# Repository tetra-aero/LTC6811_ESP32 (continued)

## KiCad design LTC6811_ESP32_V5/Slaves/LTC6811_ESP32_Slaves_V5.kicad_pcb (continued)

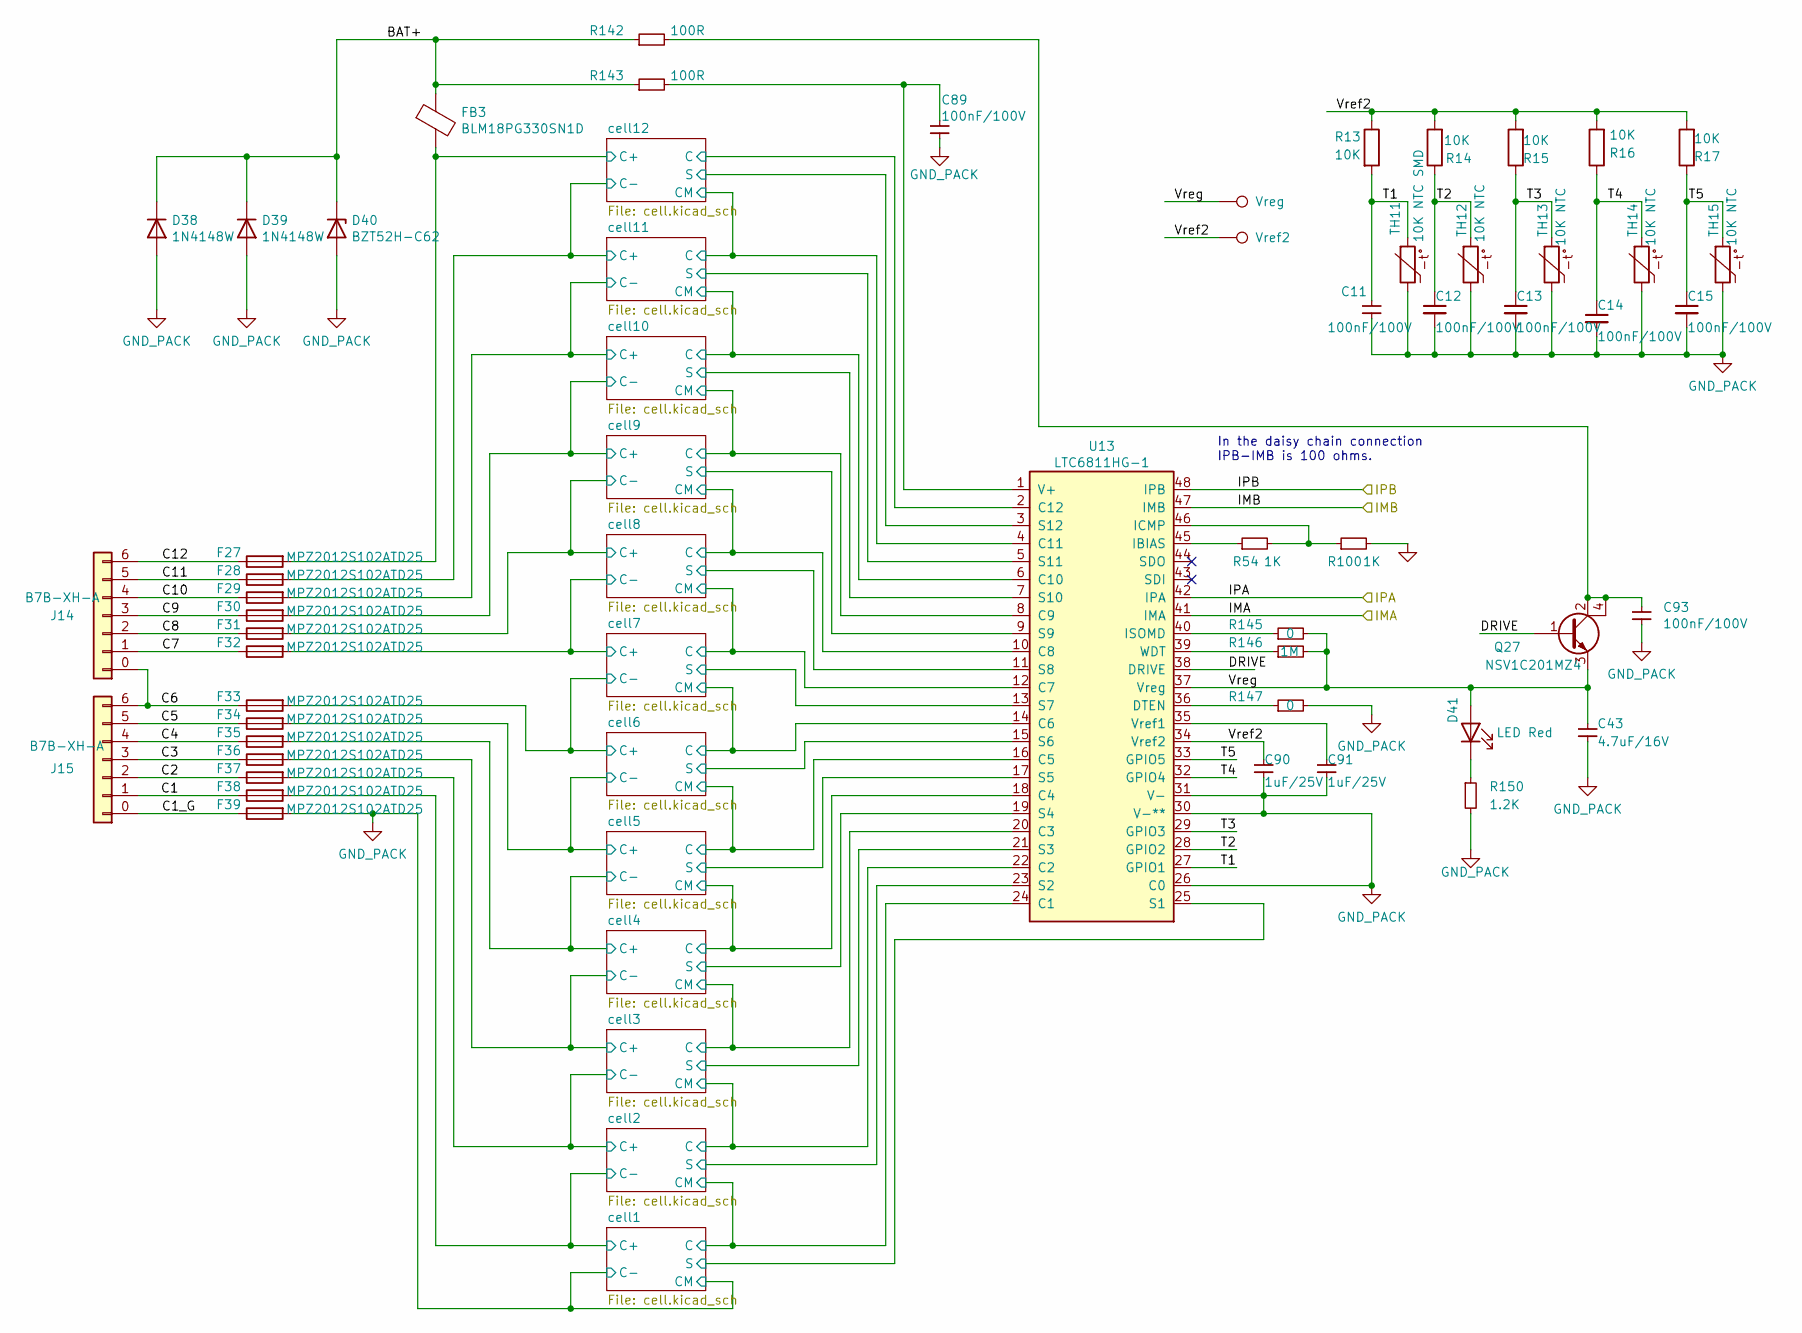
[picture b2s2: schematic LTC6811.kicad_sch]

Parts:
C11, C12, C13, C14, C15, C89, C93: 100nF/100V; C_0603_1608Metric; MPN CL10B104KC8NNNC
C43: 4.7uF/16V; C_0603_1608Metric; MPN CL10A475KO8NNNC
C90, C91: 1uF/25V; C_0603_1608Metric; MPN CL10B105KA8NNNC
D38, D39: 1N4148W; D_SOD-123; MPN 1N4148W-7-F
D40: BZT52H-C62; D_SOD-123F; MPN BZT52H-C62,115
D41: LED Red; LED_0603_1608Metric; MPN LTST-C190KRKT
F27, F28, F29, F30, F31, F32, F33, F34, F35, F36, F37, F38, F39: MPZ2012S102ATD25; Fuse_0805_2012Metric; MPN MPZ2012S102ATD25
FB3: BLM18PG330SN1D; R_0603_1608Metric; MPN BLM18PG330SN1D
J14, J15: B7B-XH-A; JST_XH_B7B-XH-A_1x07_P2.50mm_Vertical_BAT_6S; MPN B7B-XH-A
Q27: NSV1C201MZ4; SOT-223; MPN NSV1C201MZ4T1G
R13, R14, R15, R16, R17: 10K; R_0603_1608Metric; MPN RC0603FR-0710KL
R54, R100: 1K; R_0603_1608Metric; MPN RC0603FR-071KL
R142, R143: 100R; R_0603_1608Metric; MPN RC0603FR-07100RL
R145, R147: 0; R_0603_1608Metric; MPN RC0603JR-070RL
R146: 1M; R_0603_1608Metric; MPN RC0603JR-071ML
R150: 1.2K; R_0603_1608Metric; MPN RC0603JR-071K2L
TH11: 10K NTC SMD; R_0603_1608Metric; MPN NCU18XH103F6SRB
TH12, TH13, TH14, TH15: 10K NTC; R_Axial_DIN0204_L3.6mm_D1.6mm_P1.90mm_Vertical; MPN MF52C1103F3380
TP7: Vreg; TestPoint_Pad_D1.0mm
TP8: Vref2; TestPoint_Pad_D1.0mm
U13: LTC6811HG-1; TSSOP-48_6.1x12.5mm_P0.5mm; MPN LTC6811HG-1#3ZZPBF

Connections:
/LTC6811_3/BAT+: D38.1 (K), D39.1 (K), D40.1 (K), FB3.1, R142.1, R143.1
/LTC6811_3/C1: F38.1, J15.1 (Pin_2)
/LTC6811_3/C1_G: F39.1, J15.0 (Pin_1)
/LTC6811_3/C2: F37.1, J15.2 (Pin_3)
/LTC6811_3/C3: F36.1, J15.3 (Pin_4)
/LTC6811_3/C4: F35.1, J15.4 (Pin_5)
/LTC6811_3/C5: F34.1, J15.5 (Pin_6)
/LTC6811_3/C6: F33.1, J14.0 (Pin_1), J15.6 (Pin_7)
/LTC6811_3/C7: F32.1, J14.1 (Pin_2)
/LTC6811_3/C8: F31.1, J14.2 (Pin_3)
/LTC6811_3/C9: F30.1, J14.3 (Pin_4)
/LTC6811_3/C10: F29.1, J14.4 (Pin_5)
/LTC6811_3/C11: F28.1, J14.5 (Pin_6)
/LTC6811_3/C12: F27.1, J14.6 (Pin_7)
/LTC6811_3/DRIVE: Q27.1 (B), U13.38 (DRIVE)
/LTC6811_3/IMA: U13.41 (IMA); also elsewhere on the board
/LTC6811_3/IMB: U13.47 (IMB); also elsewhere on the board
/LTC6811_3/IPA: U13.42 (IPA); also elsewhere on the board
/LTC6811_3/IPB: U13.48 (IPB); also elsewhere on the board
/LTC6811_3/T1: C11.1, R13.2, TH11.1, U13.27 (GPIO1)
/LTC6811_3/T2: C12.1, R14.1, TH12.1, U13.28 (GPIO2)
/LTC6811_3/T3: C13.1, R15.1, TH13.1, U13.29 (GPIO3)
/LTC6811_3/T4: C14.1, R16.1, TH14.1, U13.32 (GPIO4)
/LTC6811_3/T5: C15.1, R17.1, TH15.1, U13.33 (GPIO5)
/LTC6811_3/Vref2: C90.1, R13.1, R14.2, R15.2, R16.2, R17.2, TP8.1, U13.34 (Vref2)
/LTC6811_3/Vreg: C43.1, D41.2 (A), Q27.3 (E), R145.2, R146.2, TP7.1, U13.37 (Vreg)
/LTC6811_3/cell1/C: U13.24 (C1); also elsewhere on the board
/LTC6811_3/cell1/C+: F38.2; also elsewhere on the board
/LTC6811_3/cell1/S: U13.25 (S1); also elsewhere on the board
/LTC6811_3/cell2/C: U13.22 (C2); also elsewhere on the board
/LTC6811_3/cell2/C+: F37.2; also elsewhere on the board
/LTC6811_3/cell2/S: U13.23 (S2); also elsewhere on the board
/LTC6811_3/cell3/C: U13.20 (C3); also elsewhere on the board
/LTC6811_3/cell3/C+: F36.2; also elsewhere on the board
/LTC6811_3/cell3/S: U13.21 (S3); also elsewhere on the board
/LTC6811_3/cell4/C: U13.18 (C4); also elsewhere on the board
/LTC6811_3/cell4/C+: F35.2; also elsewhere on the board
/LTC6811_3/cell4/S: U13.19 (S4); also elsewhere on the board
/LTC6811_3/cell5/C: U13.16 (C5); also elsewhere on the board
/LTC6811_3/cell5/C+: F34.2; also elsewhere on the board
/LTC6811_3/cell5/S: U13.17 (S5); also elsewhere on the board
/LTC6811_3/cell6/C: U13.14 (C6); also elsewhere on the board
/LTC6811_3/cell6/C+: F33.2; also elsewhere on the board
/LTC6811_3/cell6/S: U13.15 (S6); also elsewhere on the board
/LTC6811_3/cell7/C: U13.12 (C7); also elsewhere on the board
/LTC6811_3/cell7/C+: F32.2; also elsewhere on the board
/LTC6811_3/cell7/S: U13.13 (S7); also elsewhere on the board
/LTC6811_3/cell8/C: U13.10 (C8); also elsewhere on the board
/LTC6811_3/cell8/C+: F31.2; also elsewhere on the board
/LTC6811_3/cell8/S: U13.11 (S8); also elsewhere on the board
/LTC6811_3/cell9/S: U13.9 (S9); also elsewhere on the board
/LTC6811_3/cell10/C: U13.6 (C10); also elsewhere on the board
/LTC6811_3/cell10/C+: F29.2; also elsewhere on the board
/LTC6811_3/cell10/C-: F30.2; also elsewhere on the board
/LTC6811_3/cell10/CM: U13.8 (C9); also elsewhere on the board
/LTC6811_3/cell10/S: U13.7 (S10); also elsewhere on the board
/LTC6811_3/cell11/C: U13.4 (C11); also elsewhere on the board
/LTC6811_3/cell11/C+: F28.2; also elsewhere on the board
/LTC6811_3/cell11/S: U13.5 (S11); also elsewhere on the board
/LTC6811_3/cell12/C: U13.2 (C12); also elsewhere on the board
/LTC6811_3/cell12/C+: F27.2, FB3.2; also elsewhere on the board
/LTC6811_3/cell12/S: U13.3 (S12); also elsewhere on the board
GND_PACK: C11.2, C12.2, C13.2, C14.2, C15.2, C43.2, C89.2, C90.2, C91.2, C93.2, D38.2 (A), D39.2 (A), D40.2 (A), F39.2, R100.2, R147.2, R150.2, TH11.2, TH12.2, TH13.2, TH14.2, TH15.2, U13.26 (C0), U13.30 (V-**), U13.31 (V-); also elsewhere on the board
unnamed: C93.1, Q27.2 (C), Q27.4 (C), R142.2
unnamed: D41.1 (K), R150.1
unnamed: R147.1, U13.36 (DTEN)
unnamed: R54.1, U13.45 (IBIAS)
unnamed: R54.2, R100.1, U13.46 (ICMP)
unnamed: R145.1, U13.40 (ISOMD)
unnamed: C89.1, R143.2, U13.1 (V+)
unnamed: C91.1, U13.35 (Vref1)
unnamed: R146.1, U13.39 (WDT)

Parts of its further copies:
C16, C17, C18, C19, C22, C115, C119: 100nF/100V; C_0603_1608Metric; MPN CL10B104KC8NNNC
C66: 4.7uF/16V; C_0603_1608Metric; MPN CL10A475KO8NNNC
C116, C117: 1uF/25V; C_0603_1608Metric; MPN CL10B105KA8NNNC
D54, D55: 1N4148W; D_SOD-123; MPN 1N4148W-7-F
D56: BZT52H-C62; D_SOD-123F; MPN BZT52H-C62,115
D57: LED Red; LED_0603_1608Metric; MPN LTST-C190KRKT
F40, F41, F42, F43, F44, F45, F46, F47, F48, F49, F50, F51, F52: MPZ2012S102ATD25; Fuse_0805_2012Metric; MPN MPZ2012S102ATD25
FB4: BLM18PG330SN1D; R_0603_1608Metric; MPN BLM18PG330SN1D
J16, J17: B7B-XH-A; JST_XH_B7B-XH-A_1x07_P2.50mm_Vertical_BAT_6S; MPN B7B-XH-A
Q40: NSV1C201MZ4; SOT-223; MPN NSV1C201MZ4T1G
R18, R19, R20, R21, R22: 10K; R_0603_1608Metric; MPN RC0603FR-0710KL
R93, R101: 1K; R_0603_1608Metric; MPN RC0603FR-071KL
R193, R194: 100R; R_0603_1608Metric; MPN RC0603FR-07100RL
R196, R198: 0; R_0603_1608Metric; MPN RC0603JR-070RL
R197: 1M; R_0603_1608Metric; MPN RC0603JR-071ML
R201: 1.2K; R_0603_1608Metric; MPN RC0603JR-071K2L
TH16: 10K NTC SMD; R_0603_1608Metric; MPN NCU18XH103F6SRB
TH17, TH18, TH19, TH20: 10K NTC; R_Axial_DIN0204_L3.6mm_D1.6mm_P1.90mm_Vertical; MPN MF52C1103F3380
TP9: Vreg; TestPoint_Pad_D1.0mm
TP10: Vref2; TestPoint_Pad_D1.0mm
U14: LTC6811HG-1; TSSOP-48_6.1x12.5mm_P0.5mm; MPN LTC6811HG-1#3ZZPBF

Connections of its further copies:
/LTC6811_4/BAT+: D54.1 (K), D55.1 (K), D56.1 (K), FB4.1, R193.1, R194.1
/LTC6811_4/C1: F51.1, J17.1 (Pin_2)
/LTC6811_4/C1_G: F52.1, J17.0 (Pin_1)
/LTC6811_4/C2: F50.1, J17.2 (Pin_3)
/LTC6811_4/C3: F49.1, J17.3 (Pin_4)
/LTC6811_4/C4: F48.1, J17.4 (Pin_5)
/LTC6811_4/C5: F47.1, J17.5 (Pin_6)
/LTC6811_4/C6: F46.1, J16.0 (Pin_1), J17.6 (Pin_7)
/LTC6811_4/C7: F45.1, J16.1 (Pin_2)
/LTC6811_4/C8: F44.1, J16.2 (Pin_3)
/LTC6811_4/C9: F43.1, J16.3 (Pin_4)
/LTC6811_4/C10: F42.1, J16.4 (Pin_5)
/LTC6811_4/C11: F41.1, J16.5 (Pin_6)
/LTC6811_4/C12: F40.1, J16.6 (Pin_7)
/LTC6811_4/DRIVE: Q40.1 (B), U14.38 (DRIVE)
/LTC6811_4/IMA: U14.41 (IMA); also elsewhere on the board
/LTC6811_4/IMB: U14.47 (IMB); also elsewhere on the board
/LTC6811_4/IPA: U14.42 (IPA); also elsewhere on the board
/LTC6811_4/IPB: U14.48 (IPB); also elsewhere on the board
/LTC6811_4/T1: C16.1, R18.2, TH16.1, U14.27 (GPIO1)
/LTC6811_4/T2: C17.1, R19.1, TH17.1, U14.28 (GPIO2)
/LTC6811_4/T3: C18.1, R20.1, TH18.1, U14.29 (GPIO3)
/LTC6811_4/T4: C19.1, R21.1, TH19.1, U14.32 (GPIO4)
/LTC6811_4/T5: C22.1, R22.1, TH20.1, U14.33 (GPIO5)
/LTC6811_4/Vref2: C116.1, R18.1, R19.2, R20.2, R21.2, R22.2, TP10.1, U14.34 (Vref2)
/LTC6811_4/Vreg: C66.1, D57.2 (A), Q40.3 (E), R196.2, R197.2, TP9.1, U14.37 (Vreg)
/LTC6811_4/cell1/C: U14.24 (C1); also elsewhere on the board
/LTC6811_4/cell1/C+: F51.2; also elsewhere on the board
/LTC6811_4/cell1/S: U14.25 (S1); also elsewhere on the board
/LTC6811_4/cell2/C: U14.22 (C2); also elsewhere on the board
/LTC6811_4/cell2/C+: F50.2; also elsewhere on the board
/LTC6811_4/cell2/S: U14.23 (S2); also elsewhere on the board
/LTC6811_4/cell3/C: U14.20 (C3); also elsewhere on the board
/LTC6811_4/cell3/C+: F49.2; also elsewhere on the board
/LTC6811_4/cell3/S: U14.21 (S3); also elsewhere on the board
/LTC6811_4/cell4/C: U14.18 (C4); also elsewhere on the board
/LTC6811_4/cell4/C+: F48.2; also elsewhere on the board
/LTC6811_4/cell4/S: U14.19 (S4); also elsewhere on the board
/LTC6811_4/cell5/C: U14.16 (C5); also elsewhere on the board
/LTC6811_4/cell5/C+: F47.2; also elsewhere on the board
/LTC6811_4/cell5/S: U14.17 (S5); also elsewhere on the board
/LTC6811_4/cell6/C: U14.14 (C6); also elsewhere on the board
/LTC6811_4/cell6/C+: F46.2; also elsewhere on the board
/LTC6811_4/cell6/S: U14.15 (S6); also elsewhere on the board
/LTC6811_4/cell7/C: U14.12 (C7); also elsewhere on the board
/LTC6811_4/cell7/C+: F45.2; also elsewhere on the board
/LTC6811_4/cell7/S: U14.13 (S7); also elsewhere on the board
/LTC6811_4/cell8/C: U14.10 (C8); also elsewhere on the board
/LTC6811_4/cell8/C+: F44.2; also elsewhere on the board
/LTC6811_4/cell8/S: U14.11 (S8); also elsewhere on the board
/LTC6811_4/cell9/S: U14.9 (S9); also elsewhere on the board
/LTC6811_4/cell10/C: U14.6 (C10); also elsewhere on the board
/LTC6811_4/cell10/C+: F42.2; also elsewhere on the board
/LTC6811_4/cell10/C-: F43.2; also elsewhere on the board
/LTC6811_4/cell10/CM: U14.8 (C9); also elsewhere on the board
/LTC6811_4/cell10/S: U14.7 (S10); also elsewhere on the board
/LTC6811_4/cell11/C: U14.4 (C11); also elsewhere on the board
/LTC6811_4/cell11/C+: F41.2; also elsewhere on the board
/LTC6811_4/cell11/S: U14.5 (S11); also elsewhere on the board
/LTC6811_4/cell12/C: U14.2 (C12); also elsewhere on the board
/LTC6811_4/cell12/C+: F40.2, FB4.2; also elsewhere on the board
/LTC6811_4/cell12/S: U14.3 (S12); also elsewhere on the board
GND_PACK: C16.2, C17.2, C18.2, C19.2, C22.2, C66.2, C115.2, C116.2, C117.2, C119.2, D54.2 (A), D55.2 (A), D56.2 (A), F52.2, R101.2, R198.2, R201.2, TH16.2, TH17.2, TH18.2, TH19.2, TH20.2, U14.26 (C0), U14.30 (V-**), U14.31 (V-); also elsewhere on the board
unnamed: C119.1, Q40.2 (C), Q40.4 (C), R193.2
unnamed: D57.1 (K), R201.1
unnamed: R198.1, U14.36 (DTEN)
unnamed: R93.1, U14.45 (IBIAS)
unnamed: R93.2, R101.1, U14.46 (ICMP)
unnamed: R196.1, U14.40 (ISOMD)
unnamed: C115.1, R194.2, U14.1 (V+)
unnamed: C117.1, U14.35 (Vref1)
unnamed: R197.1, U14.39 (WDT)

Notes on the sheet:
In the daisy chain connection IPB-IMB is 100 ohms.

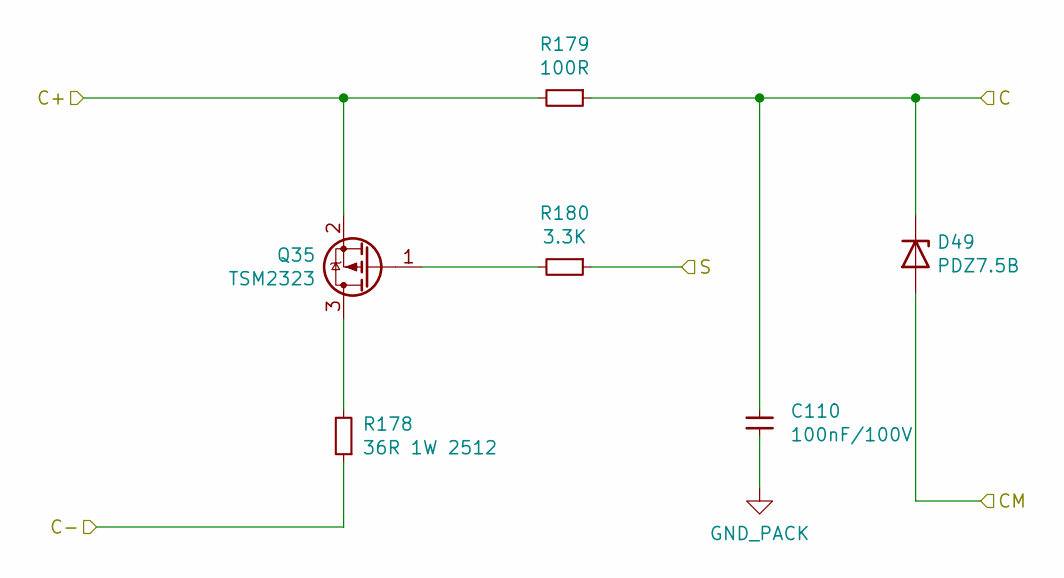
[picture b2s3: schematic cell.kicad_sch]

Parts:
C110: 100nF/100V; C_0603_1608Metric; MPN CL10B104KC8NNNC
D49: PDZ7.5B; D_SOD-323_HandSoldering; MPN PDZ7.5BZ
Q35: TSM2323; SOT-23; MPN TSM2323CX RFG
R178: 36R 1W 2512; R_2512_6332Metric; MPN RTT25360JTE
R179: 100R; R_0603_1608Metric; MPN RC0603FR-07100RL
R180: 3.3K; R_0603_1608Metric; MPN RC0603FR-073K3L

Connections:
/LTC6811_3/cell4/C: D49.2 (A); also elsewhere on the board
/LTC6811_3/cell4/C+: R178.1; also elsewhere on the board
/LTC6811_3/cell5/C: C110.1, D49.1 (K), R179.1; also elsewhere on the board
/LTC6811_3/cell5/C+: Q35.2 (S), R179.2; also elsewhere on the board
/LTC6811_3/cell5/S: R180.1; also elsewhere on the board
GND_PACK: C110.2; also elsewhere on the board
unnamed: Q35.3 (D), R178.2
unnamed: Q35.1 (G), R180.2

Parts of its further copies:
C103, C104, C105, C106, C107, C108, C109, C111, C112, C113, C114, C129, C130, C131, C132, C133, C134, C135, C136, C137, C138, C139, C140: 100nF/100V; C_0603_1608Metric; MPN CL10B104KC8NNNC
D42, D43, D44, D45, D46, D47, D48, D50, D51, D52, D53, D58, D59, D60, D61, D62, D63, D64, D65, D66, D67, D68, D69: PDZ7.5B; D_SOD-323_HandSoldering; MPN PDZ7.5BZ
Q28, Q29, Q30, Q31, Q32, Q33, Q34, Q36, Q37, Q38, Q39, Q41, Q42, Q43, Q44, Q45, Q46, Q47, Q48, Q49, Q50, Q51, Q52: TSM2323; SOT-23; MPN TSM2323CX RFG
R157, R160, R163, R166, R169, R172, R175, R181, R184, R187, R190, R208, R211, R214, R217, R220, R223, R226, R229, R232, R235, R238, R241: 36R 1W 2512; R_2512_6332Metric; MPN RTT25360JTE
R158, R161, R164, R167, R170, R173, R176, R182, R185, R188, R191, R209, R212, R215, R218, R221, R224, R227, R230, R233, R236, R239, R242: 100R; R_0603_1608Metric; MPN RC0603FR-07100RL
R159, R162, R165, R168, R171, R174, R177, R183, R186, R189, R192, R210, R213, R216, R219, R222, R225, R228, R231, R234, R237, R240, R243: 3.3K; R_0603_1608Metric; MPN RC0603FR-073K3L

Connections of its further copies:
/LTC6811_3/cell1/C: C114.1, D52.2 (A), D53.1 (K), R191.1; also elsewhere on the board
/LTC6811_3/cell1/C+: Q39.2 (S), R187.1, R191.2; also elsewhere on the board
/LTC6811_3/cell1/S: R192.1; also elsewhere on the board
/LTC6811_3/cell2/C: C113.1, D51.2 (A), D52.1 (K), R188.1; also elsewhere on the board
/LTC6811_3/cell2/C+: Q38.2 (S), R184.1, R188.2; also elsewhere on the board
/LTC6811_3/cell2/S: R189.1; also elsewhere on the board
/LTC6811_3/cell3/C: C112.1, D50.2 (A), D51.1 (K), R185.1; also elsewhere on the board
/LTC6811_3/cell3/C+: Q37.2 (S), R181.1, R185.2; also elsewhere on the board
/LTC6811_3/cell3/S: R186.1; also elsewhere on the board
/LTC6811_3/cell4/C: C111.1, D50.1 (K), R182.1; also elsewhere on the board
/LTC6811_3/cell4/C+: Q36.2 (S), R182.2; also elsewhere on the board
/LTC6811_3/cell4/S: R183.1; also elsewhere on the board
/LTC6811_3/cell5/C: D48.2 (A); also elsewhere on the board
/LTC6811_3/cell5/C+: R175.1; also elsewhere on the board
/LTC6811_3/cell6/C: C109.1, D47.2 (A), D48.1 (K), R176.1; also elsewhere on the board
/LTC6811_3/cell6/C+: Q34.2 (S), R172.1, R176.2; also elsewhere on the board
/LTC6811_3/cell6/S: R177.1; also elsewhere on the board
/LTC6811_3/cell7/C: C108.1, D46.2 (A), D47.1 (K), R173.1; also elsewhere on the board
/LTC6811_3/cell7/C+: Q33.2 (S), R169.1, R173.2; also elsewhere on the board
/LTC6811_3/cell7/S: R174.1; also elsewhere on the board
/LTC6811_3/cell8/C: C107.1, D45.2 (A), D46.1 (K), R170.1; also elsewhere on the board
/LTC6811_3/cell8/C+: Q32.2 (S), R166.1, R170.2; also elsewhere on the board
/LTC6811_3/cell8/S: R171.1; also elsewhere on the board
/LTC6811_3/cell9/S: R168.1; also elsewhere on the board
/LTC6811_3/cell10/C: C105.1, D43.2 (A), D44.1 (K), R164.1; also elsewhere on the board
/LTC6811_3/cell10/C+: Q30.2 (S), R160.1, R164.2; also elsewhere on the board
/LTC6811_3/cell10/C-: Q31.2 (S), R163.1, R167.2; also elsewhere on the board
/LTC6811_3/cell10/CM: C106.1, D44.2 (A), D45.1 (K), R167.1; also elsewhere on the board
/LTC6811_3/cell10/S: R165.1; also elsewhere on the board
/LTC6811_3/cell11/C: C104.1, D42.2 (A), D43.1 (K), R161.1; also elsewhere on the board
/LTC6811_3/cell11/C+: Q29.2 (S), R157.1, R161.2; also elsewhere on the board
/LTC6811_3/cell11/S: R162.1; also elsewhere on the board
/LTC6811_3/cell12/C: C103.1, D42.1 (K), R158.1; also elsewhere on the board
/LTC6811_3/cell12/C+: Q28.2 (S), R158.2; also elsewhere on the board
/LTC6811_3/cell12/S: R159.1; also elsewhere on the board
/LTC6811_4/cell1/C: C140.1, D68.2 (A), D69.1 (K), R242.1; also elsewhere on the board
/LTC6811_4/cell1/C+: Q52.2 (S), R238.1, R242.2; also elsewhere on the board
/LTC6811_4/cell1/S: R243.1; also elsewhere on the board
/LTC6811_4/cell2/C: C139.1, D67.2 (A), D68.1 (K), R239.1; also elsewhere on the board
/LTC6811_4/cell2/C+: Q51.2 (S), R235.1, R239.2; also elsewhere on the board
/LTC6811_4/cell2/S: R240.1; also elsewhere on the board
/LTC6811_4/cell3/C: C138.1, D66.2 (A), D67.1 (K), R236.1; also elsewhere on the board
/LTC6811_4/cell3/C+: Q50.2 (S), R232.1, R236.2; also elsewhere on the board
/LTC6811_4/cell3/S: R237.1; also elsewhere on the board
/LTC6811_4/cell4/C: C137.1, D65.2 (A), D66.1 (K), R233.1; also elsewhere on the board
/LTC6811_4/cell4/C+: Q49.2 (S), R229.1, R233.2; also elsewhere on the board
/LTC6811_4/cell4/S: R234.1; also elsewhere on the board
/LTC6811_4/cell5/C: C136.1, D64.2 (A), D65.1 (K), R230.1; also elsewhere on the board
/LTC6811_4/cell5/C+: Q48.2 (S), R226.1, R230.2; also elsewhere on the board
/LTC6811_4/cell5/S: R231.1; also elsewhere on the board
/LTC6811_4/cell6/C: C135.1, D63.2 (A), D64.1 (K), R227.1; also elsewhere on the board
/LTC6811_4/cell6/C+: Q47.2 (S), R223.1, R227.2; also elsewhere on the board
/LTC6811_4/cell6/S: R228.1; also elsewhere on the board
/LTC6811_4/cell7/C: C134.1, D62.2 (A), D63.1 (K), R224.1; also elsewhere on the board
/LTC6811_4/cell7/C+: Q46.2 (S), R220.1, R224.2; also elsewhere on the board
/LTC6811_4/cell7/S: R225.1; also elsewhere on the board
/LTC6811_4/cell8/C: C133.1, D61.2 (A), D62.1 (K), R221.1; also elsewhere on the board
/LTC6811_4/cell8/C+: Q45.2 (S), R217.1, R221.2; also elsewhere on the board
/LTC6811_4/cell8/S: R222.1; also elsewhere on the board
/LTC6811_4/cell9/S: R219.1; also elsewhere on the board
/LTC6811_4/cell10/C: C131.1, D59.2 (A), D60.1 (K), R215.1; also elsewhere on the board
/LTC6811_4/cell10/C+: Q43.2 (S), R211.1, R215.2; also elsewhere on the board
/LTC6811_4/cell10/C-: Q44.2 (S), R214.1, R218.2; also elsewhere on the board
/LTC6811_4/cell10/CM: C132.1, D60.2 (A), D61.1 (K), R218.1; also elsewhere on the board
/LTC6811_4/cell10/S: R216.1; also elsewhere on the board
/LTC6811_4/cell11/C: C130.1, D58.2 (A), D59.1 (K), R212.1; also elsewhere on the board
/LTC6811_4/cell11/C+: Q42.2 (S), R208.1, R212.2; also elsewhere on the board
/LTC6811_4/cell11/S: R213.1; also elsewhere on the board
/LTC6811_4/cell12/C: C129.1, D58.1 (K), R209.1; also elsewhere on the board
/LTC6811_4/cell12/C+: Q41.2 (S), R209.2; also elsewhere on the board
/LTC6811_4/cell12/S: R210.1; also elsewhere on the board
GND_PACK: C103.2, C104.2, C105.2, C106.2, C107.2, C108.2, C109.2, C111.2, C112.2, C113.2, C114.2, C129.2, C130.2, C131.2, C132.2, C133.2, C134.2, C135.2, C136.2, C137.2, C138.2, C139.2, C140.2, D53.2 (A), D69.2 (A), R190.1, R241.1; also elsewhere on the board
unnamed: Q28.3 (D), R157.2
unnamed: Q28.1 (G), R159.2
unnamed: Q29.3 (D), R160.2
unnamed: Q29.1 (G), R162.2
unnamed: Q30.3 (D), R163.2
unnamed: Q30.1 (G), R165.2
unnamed: Q31.3 (D), R166.2
unnamed: Q31.1 (G), R168.2
unnamed: Q32.3 (D), R169.2
unnamed: Q32.1 (G), R171.2
unnamed: Q33.3 (D), R172.2
unnamed: Q33.1 (G), R174.2
unnamed: Q34.3 (D), R175.2
unnamed: Q34.1 (G), R177.2
unnamed: Q36.3 (D), R181.2
unnamed: Q36.1 (G), R183.2
unnamed: Q37.3 (D), R184.2
unnamed: Q37.1 (G), R186.2
unnamed: Q38.3 (D), R187.2
unnamed: Q38.1 (G), R189.2
unnamed: Q39.3 (D), R190.2
unnamed: Q39.1 (G), R192.2
unnamed: Q41.3 (D), R208.2
unnamed: Q41.1 (G), R210.2
unnamed: Q42.3 (D), R211.2
unnamed: Q42.1 (G), R213.2
unnamed: Q43.3 (D), R214.2
unnamed: Q43.1 (G), R216.2
unnamed: Q44.3 (D), R217.2
unnamed: Q44.1 (G), R219.2
unnamed: Q45.3 (D), R220.2
unnamed: Q45.1 (G), R222.2
unnamed: Q46.3 (D), R223.2
unnamed: Q46.1 (G), R225.2
unnamed: Q47.3 (D), R226.2
unnamed: Q47.1 (G), R228.2
unnamed: Q48.3 (D), R229.2
unnamed: Q48.1 (G), R231.2
unnamed: Q49.3 (D), R232.2
unnamed: Q49.1 (G), R234.2
unnamed: Q50.3 (D), R235.2
unnamed: Q50.1 (G), R237.2
unnamed: Q51.3 (D), R238.2
unnamed: Q51.1 (G), R240.2
unnamed: Q52.3 (D), R241.2
unnamed: Q52.1 (G), R243.2

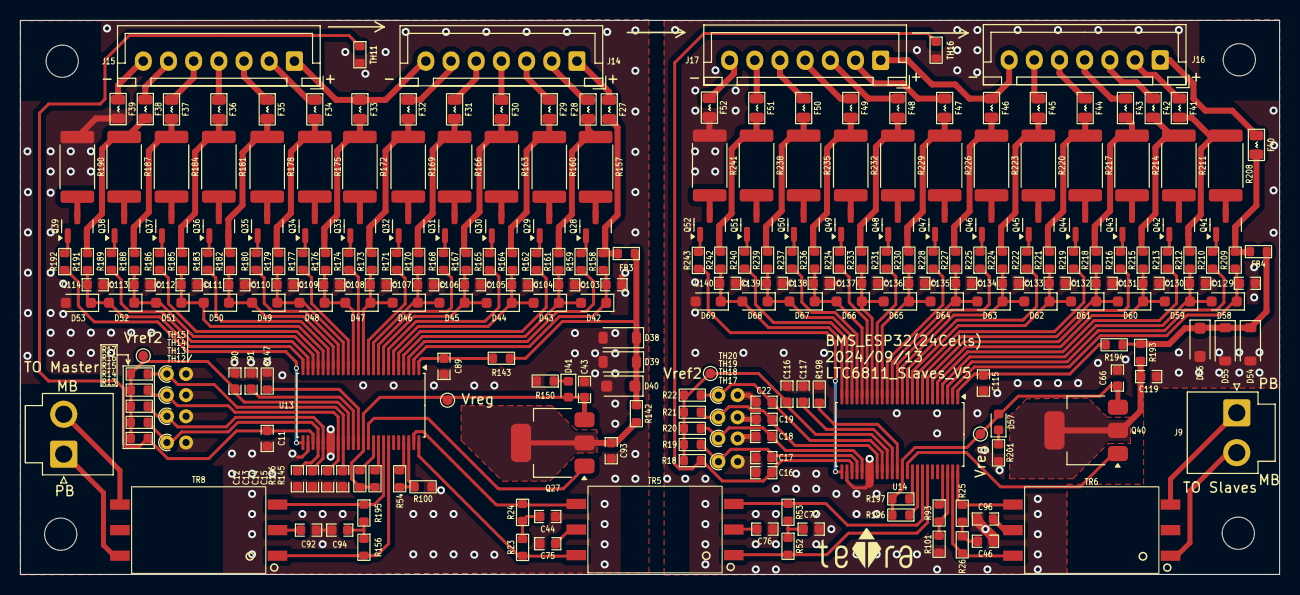
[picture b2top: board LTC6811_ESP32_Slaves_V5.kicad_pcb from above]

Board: 2 copper layers, 125.0 x 55.0 mm, 275 parts (1 on the bottom side), 203 nets.

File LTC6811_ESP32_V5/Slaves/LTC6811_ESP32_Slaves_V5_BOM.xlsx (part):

Item | Qty | Reference | Value | Description | Datasheet | Footprint | Link | MPN
1 | 38 | C11,C12,C13,C14,C15,C16,C17,C18,C19,C22,C89,C93,C103,C104,C105,C106,C107,C108,C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 | 100nF/100V | 0.1 uF ±10% 100V Ceramic Capacitor X7R 0603 (1608 Metric) | https://www.digikey.jp/en/products/detail/samsung-electro-me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 | Capacitor_SMD:C_0603_1608Metric | https://www.digikey.jp/en/products/detail/samsung-electro-me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 | CL10B104KC8NNNC
2 | 2 | C43,C66 | 4.7uF/16V | 4.7 uF ±10% 16V Ceramic Capacitor X5R 0603 (1608 Metric) | https://mm.digikey.com/Volume0/opasdata/d220001/medias/docus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 | Capacitor_SMD:C_0603_1608Metric | https://www.digikey.jp/en/products/detail/samsung-electro-me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 | CL10A475KO8NNNC
3 | 8 | C44,C46,C72,C75,C76,C92,C94,C96 | 10nF/100V | 10000 pF ±10% 100V Ceramic Capacitor X7R 0603 (1608 Metric) | https://content.kemet.com/datasheets/KEM_X7R_FT_VW_AUDI.pdf | Capacitor_SMD:C_0603_1608Metric | https://www.digikey.jp/en/products/detail/kemet/C0603X103K1R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 | C0603X103K1RAC3316
4 | 4 | C90,C91,C116,C117 | 1uF/25V | 1 uF ±10% 25V Ceramic Capacitor X7R 0603 (1608 Metric) | https://mm.digikey.com/Volume0/opasdata/d220001/medias/docus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 | Capacitor_SMD:C_0603_1608Metric | https://www.digikey.jp/en/products/detail/samsung-electro-me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 | CL10B105KA8NNNC
5 | 4 | D38,D39,D54,D55 | 1N4148W | Diode 100 V 300mA Surface Mount SOD-123 | https://www.diodes.com/assets/Datasheets/BAV16W_1N4148W.pdf | Diode_SMD:D_SOD-123 | https://www.digikey.jp/en/products/detail/diodes-incorporate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 | 1N4148W-7-F
6 | 2 | D40,D56 | BZT52H-C62 | Zener Diode 62 V 375 mW ±5% Surface Mount SOD-123F | https://assets.nexperia.com/documents/data-sheet/BZT52H_SER.pdf | Diode_SMD:D_SOD-123F | https://www.digikey.jp/en/products/detail/nexperia-usa-inc/B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 | BZT52H-C62,115
7 | 2 | D41,D57 | LED Red | Red 631nm LED Indication - Discrete 2V 0603 (1608 Metric) | https://optoelectronics.liteon.com/upload/download/DS-22-99-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 | LED_SMD:LED_0603_1608Metric | https://www.digikey.jp/en/products/detail/liteon/LTST-C190KR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 | LTST-C190KRKT
8 | 24 | D42,D43,D44,D45,D46,D47,D48,D49,D50,D51,D52,D53,D58,D59,D60,D61,D62,D63,D64,D65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 | PDZ7.5B | Zener Diode 7.6 V 400 mW ±2% Surface Mount SOD-323 | https://assets.nexperia.com/documents/data-sheet/PDZ-B_SER.pdf | Diode_SMD:D_SOD-323_HandSoldering | https://www.digikey.jp/en/products/detail/nexperia-usa-inc/P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 | PDZ7.5BZ
9 | 26 | F27,F28,F29,F30,F31,F32,F33,F34,F35,F36,F37,F38,F39,F40,F41,F42,F43,F44,F45,F46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 | MPZ2012S102ATD25 | 1 kOhms @ 100 MHz 1 Power Line Ferrite Bead 0805 (2012 Metric) 1.5A 150mOhm | https://product.tdk.com/en/system/files?file=dam/doc/product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 | Fuse:Fuse_0805_2012Metric | https://www.digikey.jp/en/products/detail/tdk-corporation/MP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 | MPZ2012S102ATD25
10 | 2 | FB3,FB4 | BLM18PG330SN1D | 33 Ohms @ 100 MHz 1 Power Line Ferrite Bead 0603 (1608 Metric) 3A 25mOhm | https://www.murata.com/en-us/products/productdata/8796738650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 | Resistor_SMD:R_0603_1608Metric | https://www.digikey.jp/en/products/detail/murata-electronics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 | BLM18PG330SN1D
11 | 4 | J14,J15,J16,J17 | B7B-XH-A | Connector Header Through Hole 7 position 0.098" (2.50mm) | https://www.jst-mfg.com/product/pdf/eng/eXH.pdf | Connector_JST:JST_XH_B7B-XH-A_1x07_P2.50mm_Vertical_BAT_6S | https://www.digikey.jp/en/products/detail/jst-sales-america-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 | B7B-XH-A
12 | 2 | J9,J22 | B2P-VH-B | Connector Header Through Hole 2 position 0.100" (2.54mm) | https://tools.molex.com/pdm_docs/sd/705430001_sd.pdf | Connector_JST:JST_VH_B2P-VH-B_1x02_P3.96mm_Vertical | https://www.digikey.jp/en/products/detail/jst-sales-america-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 | B2P-VH
13 | 2 | Q27,Q40 | NSV1C201MZ4 | Bipolar (BJT) Transistor NPN 100 V 2 A 100MHz 800 mW Surface Mount SOT-223 (TO-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 | https://www.onsemi.com/pdf/datasheet/nss1c201mz4-d.pdf | Package_TO_SOT_SMD:SOT-223 | https://www.digikey.jp/en/products/detail/onsemi/NSV1C201MZ4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 | NSV1C201MZ4T1G
14 | 24 | Q28,Q29,Q30,Q31,Q32,Q33,Q34,Q35,Q36,Q37,Q38,Q39,Q41,Q42,Q43,Q44,Q45,Q46,Q47,Q48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 | TSM2323 | P-Channel 20 V 4.7A (Ta) 1.25W (Ta) Surface Mount SOT-23 | https://www.taiwansemi.com/assets/uploads/datasheet/TSM2323_F15.pdf | Package_TO_SOT_SMD:SOT-23 | https://www.digikey.jp/en/products/detail/taiwan-semiconduct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 | TSM2323CX RFG
15 | 10 | R13,R14,R15,R16,R17,R18,R19,R20,R21,R22 | 10K | 10 kOhms ±1% 0.1W, 1/10W Chip Resistor 0603 (1608 Metric) Moisture Resistant Th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 | https://www.yageo.com/upload/media/product/products/datashee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 | Resistor_SMD:R_0603_1608Metric | https://www.digikey.jp/en/products/detail/yageo/RC0603FR-071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 | RC0603FR-0710KL
16 | 28 | R142,R143,R158,R161,R164,R167,R170,R173,R176,R179,R182,R185,R188,R191,R193,R194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 | 100R | 100 Ohms ±1% 0.1W, 1/10W Chip Resistor 0603 (1608 Metric) Moisture Resistant Th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 | https://www.yageo.com/upload/media/product/app/datasheet/rch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 | Resistor_SMD:R_0603_1608Metric | https://www.digikey.jp/en/products/detail/yageo/RC0603FR-071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 | RC0603FR-07100RL
17 | 4 | R145,R147,R196,R198 | 0 | 0 Ohms Jumper Chip Resistor 0603 (1608 Metric) Moisture Resistant Thick Film | https://www.yageo.com/upload/media/product/products/datashee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 | Resistor_SMD:R_0603_1608Metric | https://www.digikey.jp/en/products/detail/yageo/RC0603JR-070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 | RC0603JR-070RL
18 | 2 | R146,R197 | 1M | 1 MOhms ±5% 0.1W, 1/10W Chip Resistor 0603 (1608 Metric) Moisture Resistant Thi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 | https://www.yageo.com/upload/media/product/app/datasheet/rch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 | Resistor_SMD:R_0603_1608Metric | https://www.digikey.jp/en/products/detail/yageo/RC0603JR-071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 | RC0603JR-071ML
19 | 2 | R150,R201 | 1.2K | 1.2 kOhms ±5% 0.1W, 1/10W Chip Resistor 0603 (1608 Metric) Moisture Resistant T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 | https://www.yageo.com/upload/media/product/productsearch/dat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 | Resistor_SMD:R_0603_1608Metric | https://www.digikey.jp/en/products/detail/yageo/RC0603JR-071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 | RC0603JR-071K2L
20 | 24 | R157,R160,R163,R166,R169,R172,R175,R178,R181,R184,R187,R190,R208,R211,R214,R217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 | 36R 1W 2512 | 36 Ohms ±5% 1W Chip Resistor 2512 (6432 Metric) Automotive AEC-Q200 Thick Film | https://www.seielect.com/catalog/sei-rmcf_rmcp.pdf | Resistor_SMD:R_2512_6332Metric | https://www.digikey.jp/en/products/detail/stackpole-electron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 | RTT25360JTE
21 | 24 | R159,R162,R165,R168,R171,R174,R177,R180,R183,R186,R189,R192,R210,R213,R216,R219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 | 3.3K | 3.3 kOhms ±1% 0.1W, 1/10W Chip Resistor 0603 (1608 Metric) Moisture Resistant T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 | https://www.yageo.com/upload/media/product/app/datasheet/rch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 | Resistor_SMD:R_0603_1608Metric | https://www.digikey.jp/en/products/detail/yageo/RC0603FR-073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 | RC0603FR-073K3L
22 | 4 | R23,R24,R52,R53 | 49.9R | 49.9 Ohms ±1% 0.1W, 1/10W Chip Resistor 0603 (1608 Metric) Automotive AEC-Q200 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 | https://industrial.panasonic.com/cdbs/www-data/pdf/RDA0000/A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 | Resistor_SMD:R_0603_1608Metric | https://www.digikey.jp/en/products/detail/panasonic-electron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 | ERJ-3EKF49R9V
23 | 4 | R25,R26,R156,R195 | 51R | 51 Ohms ±5% 0.1W, 1/10W Chip Resistor 0603 (1608 Metric) Moisture Resistant Thi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 | https://www.yageo.com/upload/media/product/productsearch/dat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 | Resistor_SMD:R_0603_1608Metric | https://www.digikey.jp/en/products/detail/yageo/RC0603JR-075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 | RC0603JR-0751RL
24 | 4 | R54,R93,R100,R101 | 1K | 1 kOhms ±1% 0.1W, 1/10W Chip Resistor 0603 (1608 Metric) Moisture Resistant Thi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 | https://www.yageo.com/upload/media/product/products/datashee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 | Resistor_SMD:R_0603_1608Metric | https://www.digikey.jp/en/products/detail/yageo/RC0603FR-071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 | RC0603FR-071KL
25 | 2 | TH11,TH16 | 10K NTC SMD | THERMISTOR NTC 10KOHM 3380K 0603 | https://www.murata.com/en-us/api/pdfdownloadapi?cate=luNTCfo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 | Resistor_SMD:R_0603_1608Metric | https://www.digikey.jp/en/products/detail/murata-electronics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 | NCU18XH103F6SRB
26 | 8 | TH12,TH13,TH14,TH15,TH17,TH18,TH19,TH20 | 10K NTC | THERMISTOR NTC 10KOHM 3380K BEAD | https://www.cantherm.com/wp-content/uploads/2017/05/cantherm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 | Resistor_THT:R_Axial_DIN0204_L3.6mm_D1.6mm_P1.90mm_Vertical | https://www.digikey.jp/en/products/detail/cantherm/MF52C1103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 | MF52C1103F3380
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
